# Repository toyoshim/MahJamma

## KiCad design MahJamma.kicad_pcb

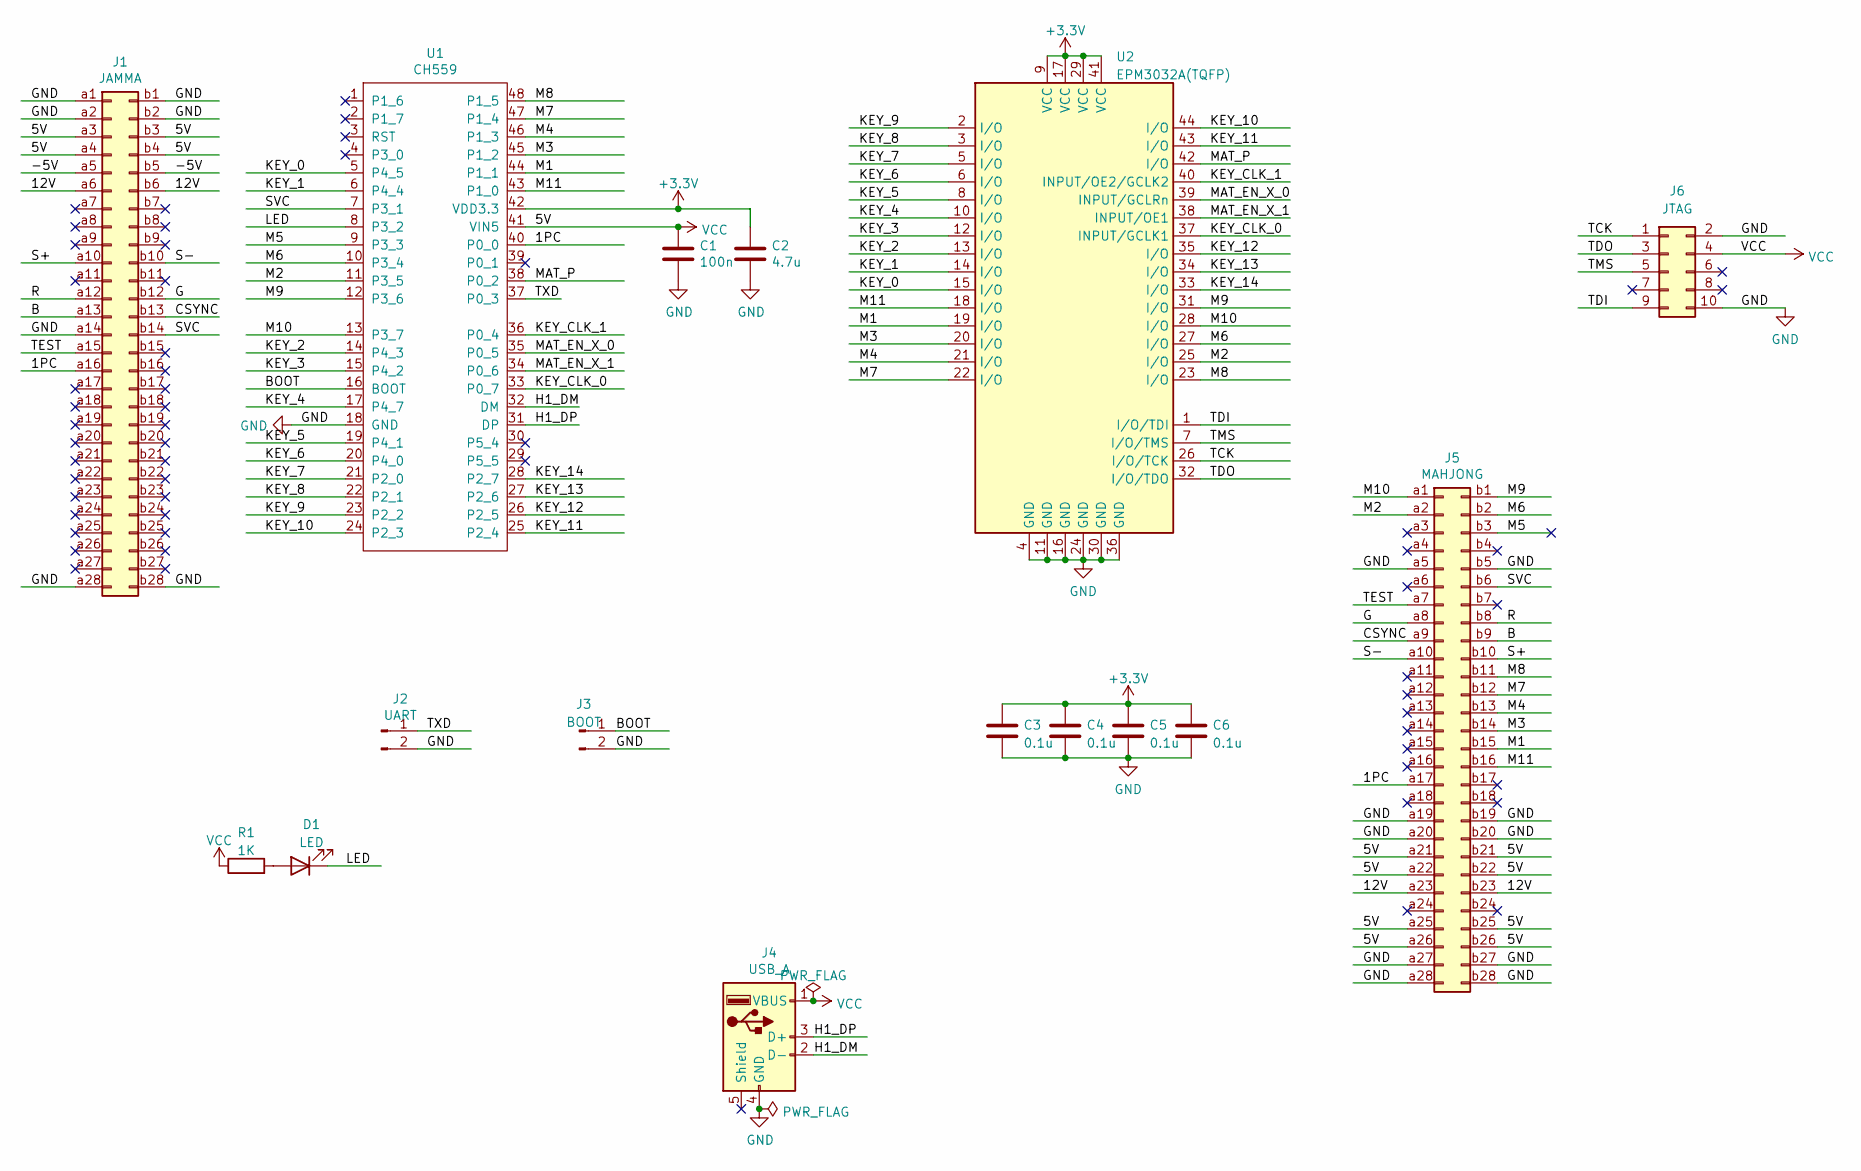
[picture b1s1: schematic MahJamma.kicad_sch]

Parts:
C1: 100n; C_0603_1608Metric_Pad1.08x0.95mm_HandSolder
C2: 4.7u; C_0603_1608Metric_Pad1.08x0.95mm_HandSolder
C3, C4, C5, C6: 0.1u; C_0603_1608Metric_Pad1.08x0.95mm_HandSolder
D1: LED; LED_0603_1608Metric_Pad1.05x0.95mm_HandSolder
J1: JAMMA; Connector_Edge_3.96mm_02x28_Row_JAMMA
J2: UART; PinHeader_1x02_P2.54mm_Vertical
J3: BOOT; PinHeader_1x02_P2.54mm_Vertical
J4: USB_A; USB_A_Female_UE27AC54100
J5: MAHJONG; Connector_Edge_3.96mm_02x28_Row_JAMMA
J6: JTAG; PinHeader_2x05_P2.54mm_Vertical
R1: 1K; R_0603_1608Metric_Pad0.98x0.95mm_HandSolder
U1: CH559; LQFP-48_7x7mm_P0.5mm
U2: EPM3032A(TQFP); TQFP-44_10x10mm_P0.8mm

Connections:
+3.3V: C2.1, C3.1, C4.1, C5.1, C6.1, U1.42 (VDD3.3), U2.9 (VCC), U2.17 (VCC), U2.29 (VCC), U2.41 (VCC)
/1PC: J1.a16, J5.a17, U1.40 (P0_0)
/12V: J1.a6, J1.b6, J5.a23, J5.b23
/-5V: J1.a5, J1.b5
/B: J1.a13, J5.b9
/BOOT: J3.1, U1.16 (BOOT)
/CSYNC: J1.b13, J5.a9
/G: J1.b12, J5.a8
/H1_DM: J4.2 (D-), U1.32 (DM)
/H1_DP: J4.3 (D+), U1.31 (DP)
/KEY_0: U1.5 (P4_5), U2.15 (I/O)
/KEY_1: U1.6 (P4_4), U2.14 (I/O)
/KEY_2: U1.14 (P4_3), U2.13 (I/O)
/KEY_3: U1.15 (P4_2), U2.12 (I/O)
/KEY_4: U1.17 (P4_7), U2.10 (I/O)
/KEY_5: U1.19 (P4_1), U2.8 (I/O)
/KEY_6: U1.20 (P4_0), U2.6 (I/O)
/KEY_7: U1.21 (P2_0), U2.5 (I/O)
/KEY_8: U1.22 (P2_1), U2.3 (I/O)
/KEY_9: U1.23 (P2_2), U2.2 (I/O)
/KEY_10: U1.24 (P2_3), U2.44 (I/O)
/KEY_11: U1.25 (P2_4), U2.43 (I/O)
/KEY_12: U1.26 (P2_5), U2.35 (I/O)
/KEY_13: U1.27 (P2_6), U2.34 (I/O)
/KEY_14: U1.28 (P2_7), U2.33 (I/O)
/KEY_CLK_0: U1.33 (P0_7), U2.37 (INPUT/GCLK1)
/KEY_CLK_1: U1.36 (P0_4), U2.40 (INPUT/OE2/GCLK2)
/LED: D1.1 (K), U1.8 (P3_2)
/M1: J5.b15, U1.44 (P1_1), U2.19 (I/O)
/M2: J5.a2, U1.11 (P3_5), U2.25 (I/O)
/M3: J5.b14, U1.45 (P1_2), U2.20 (I/O)
/M4: J5.b13, U1.46 (P1_3), U2.21 (I/O)
/M5: J5.b3, U1.9 (P3_3)
/M6: J5.b2, U1.10 (P3_4), U2.27 (I/O)
/M7: J5.b12, U1.47 (P1_4), U2.22 (I/O)
/M8: J5.b11, U1.48 (P1_5), U2.23 (I/O)
/M9: J5.b1, U1.12 (P3_6), U2.31 (I/O)
/M10: J5.a1, U1.13 (P3_7), U2.28 (I/O)
/M11: J5.b16, U1.43 (P1_0), U2.18 (I/O)
/MAT_EN_X_0: U1.35 (P0_5), U2.39 (INPUT/GCLRn)
/MAT_EN_X_1: U1.34 (P0_6), U2.38 (INPUT/OE1)
/MAT_P: U1.38 (P0_2), U2.42 (I/O)
/R: J1.a12, J5.b8
/S+: J1.a10, J5.b10
/S-: J1.b10, J5.a10
/SVC: J1.b14, J5.b6, U1.7 (P3_1)
/TCK: J6.1, U2.26 (I/O/TCK)
/TDI: J6.9, U2.1 (I/O/TDI)
/TDO: J6.3, U2.32 (I/O/TDO)
/TEST: J1.a15, J5.a7
/TMS: J6.5, U2.7 (I/O/TMS)
/TXD: J2.1, U1.37 (P0_3)
GND: C1.2, C2.2, C3.2, C4.2, C5.2, C6.2, J1.a1, J1.a2, J1.a14, J1.a28, J1.b1, J1.b2, J1.b28, J2.2, J3.2, J4.4 (GND), J5.a5, J5.a19, J5.a20, J5.a27, J5.a28, J5.b5, J5.b19, J5.b20, J5.b27, J5.b28, J6.2, J6.10, U1.18 (GND), U2.4 (GND), U2.11 (GND), U2.16 (GND), U2.24 (GND), U2.30 (GND), U2.36 (GND)
unnamed: D1.2 (A), R1.2
VCC: C1.1, J1.a3, J1.a4, J1.b3, J1.b4, J4.1 (VBUS), J5.a21, J5.a22, J5.a25, J5.a26, J5.b21, J5.b22, J5.b25, J5.b26, J6.4, R1.1, U1.41 (VIN5)

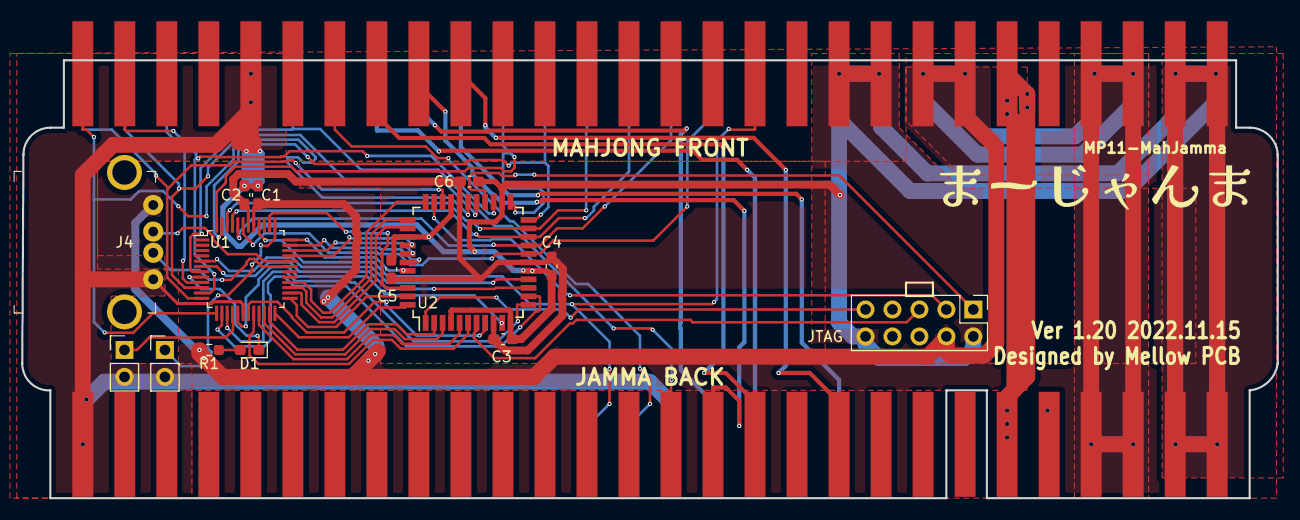
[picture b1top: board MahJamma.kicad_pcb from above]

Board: 2 copper layers, 118.3 x 41.3 mm, 17 parts (1 on the bottom side), 55 nets.

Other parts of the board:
G1: LOGO; mahjamma

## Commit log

2022-09-08 Add submodules
2022-09-10 experimental impl
    it sill has timing issues and probably requires pcb changes to
    support external mux to realize quick output selection.
2022-10-11 pcb v1.10
2022-11-13 Add initial logic for EPM3032A that can be built with Quartus II
    but it seems a little large and requires 64 cells...
2022-11-13 complete the logic that fits
2022-11-14 v1.20
